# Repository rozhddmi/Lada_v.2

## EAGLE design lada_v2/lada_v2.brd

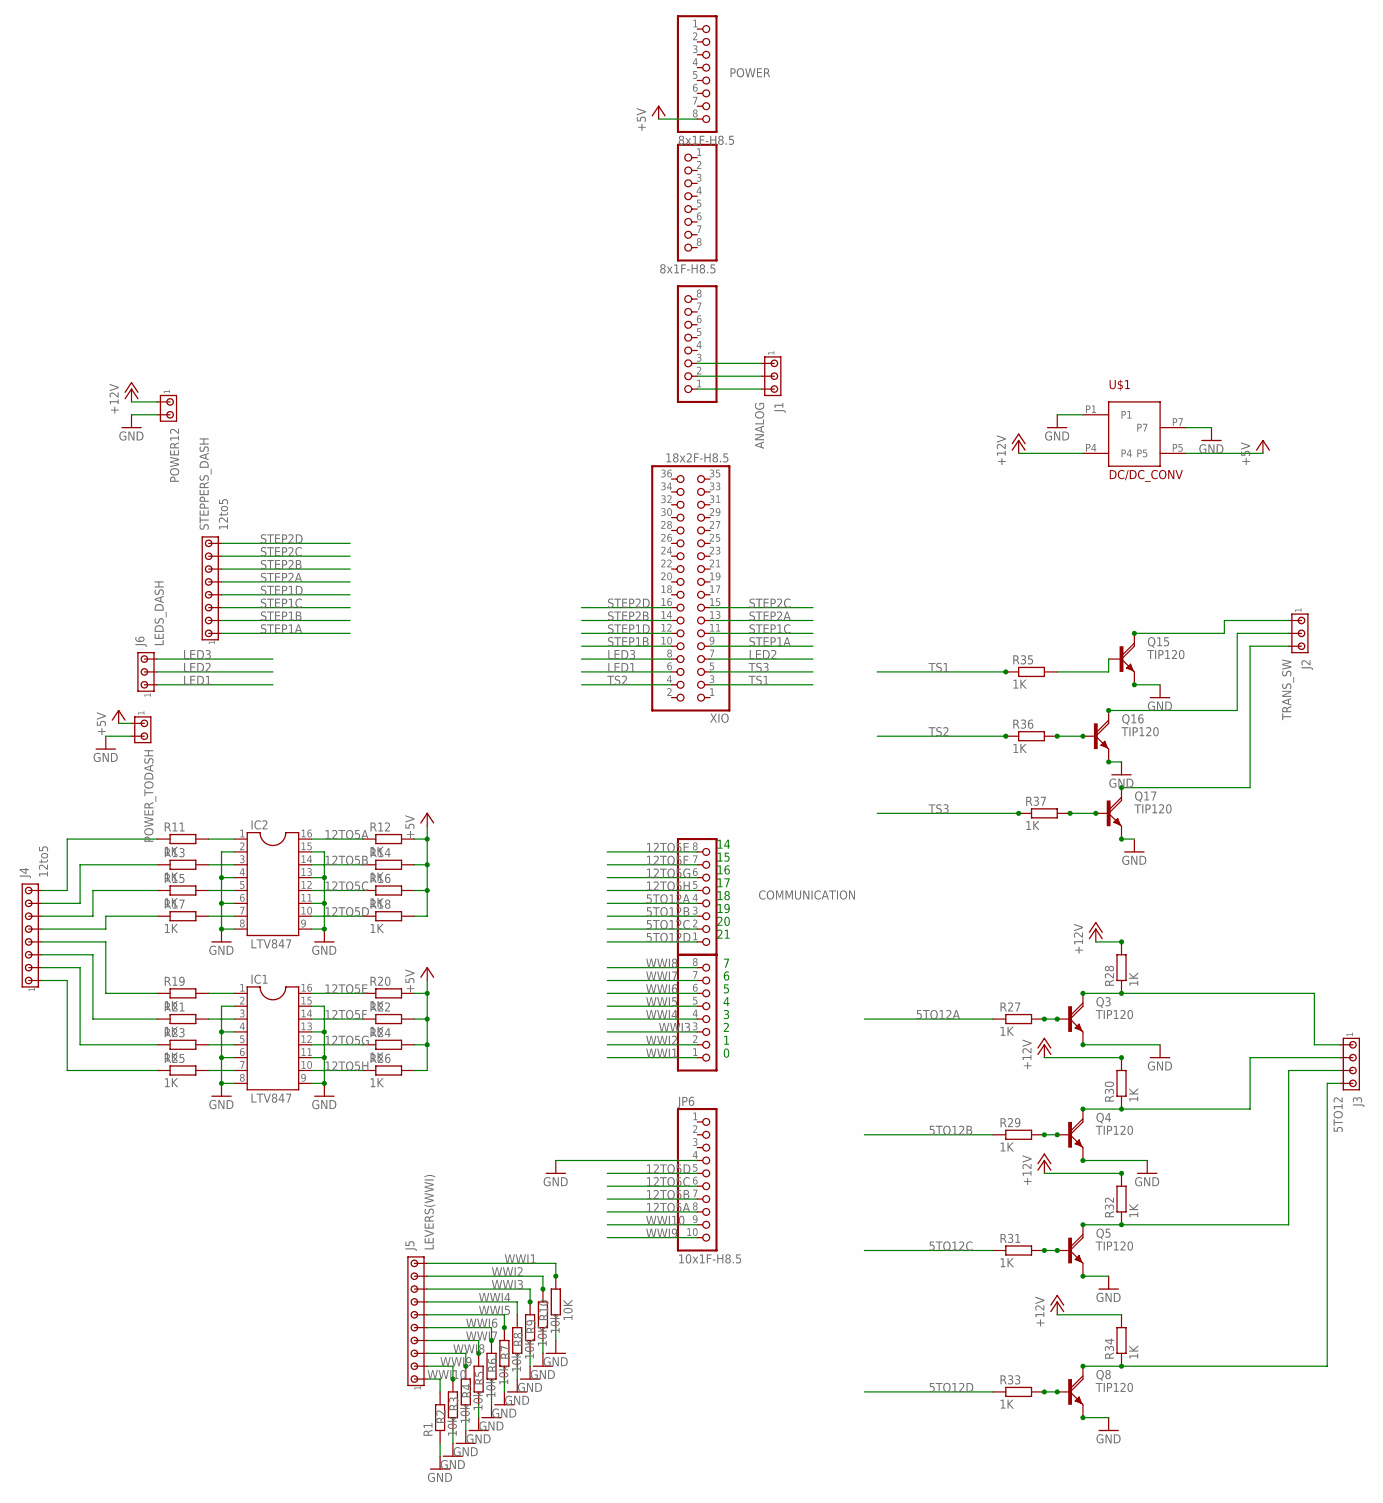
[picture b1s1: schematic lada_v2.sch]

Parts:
ADCH: 8x1F-H8.5; 1X08
ADCL: 8x1F-H8.5; 1X08
COMMUNICATION: 8x1F-H8.5; 1X08
IC1, IC2: LTV847; DIL16
J1: ANALOG; 10X03MTA
J2: TRANS_SW; 10X03MTA
J3: 5TO12; 10X04MTA
J4: 12to5; 10X08MTA
J5: LEVERS(WWI); 10X10MTA
J6: LEDS_DASH; 10X03MTA
JP6: 10x1F-H8.5; 1X10
POWER: 8x1F-H8.5; 1X08
POWER12: MTA02-100; 10X02MTA
POWER_TODASH: MTA02-100; 10X02MTA
PWML: 8x1F-H8.5; 1X08
Q3, Q4, Q5, Q8, Q15, Q16, Q17: TIP120; TO220AH
R1, R2, R3, R4, R5, R6, R9: 10k; 0207/10
R7, R8, R10: 10K; 0207/10
R11, R12, R13, R14, R15, R16, R17, R18, R19, R20, R21, R22, R23, R24, R25, R26, R27, R28, R29, R30, R31, R32, R33, R34, R35, R36, R37: 1K; 0207/10
STEPPERS_DASH: 12to5; 10X08MTA
U$1: DC/DC_CONV
XIO: 18x2F-H8.5; 2X18

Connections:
5TO12A: COMMUNICATION.4, R27.1
5TO12B: COMMUNICATION.3, R29.1
5TO12C: COMMUNICATION.2, R31.1
5TO12D: COMMUNICATION.1, R33.1
12TO5A: IC2.16, JP6.8, R12.1
12TO5B: IC2.14, JP6.7, R14.1
12TO5C: IC2.12, JP6.6, R16.1
12TO5D: IC2.10, JP6.5, R18.1
12TO5E: COMMUNICATION.8, IC1.16, R20.1
12TO5F: COMMUNICATION.7, IC1.14, R22.1
12TO5G: COMMUNICATION.6, IC1.12, R24.1
12TO5H: COMMUNICATION.5, IC1.10, R26.1
+5V: POWER.8, POWER_TODASH.1, R12.2, R14.2, R16.2, R18.2, R20.2, R22.2, R24.2, R26.2, U$1.P5
+12V: POWER12.1, R28.2, R30.2, R32.2, R34.2, U$1.P4
GND: IC1.2, IC1.4, IC1.6, IC1.8, IC1.9, IC1.11, IC1.13, IC1.15, IC2.2, IC2.4, IC2.6, IC2.8, IC2.9, IC2.11, IC2.13, IC2.15, JP6.4, POWER12.2, POWER_TODASH.2, Q3.E, Q4.E, Q5.E, Q8.E, Q15.E, Q16.E, Q17.E, R1.1, R2.1, R3.1, R4.1, R5.1, R6.1, R7.1, R8.1, R9.1, R10.1, U$1.P1, U$1.P7
LED1: J6.1, XIO.6
LED2: J6.2, XIO.7
LED3: J6.3, XIO.8
unnamed: ADCH.1, J1.3
unnamed: Q15.B, R35.2
unnamed: ADCH.2, J1.2
unnamed: ADCH.3, J1.1
unnamed: J3.1, Q3.C, R28.1
unnamed: J3.2, Q4.C, R30.1
unnamed: J3.3, Q5.C, R32.1
unnamed: Q5.B, R31.2
unnamed: Q4.B, R29.2
unnamed: Q3.B, R27.2
unnamed: J3.4, Q8.C, R34.1
unnamed: Q8.B, R33.2
unnamed: J2.1, Q15.C
unnamed: J2.2, Q16.C
unnamed: Q16.B, R36.2
unnamed: J2.3, Q17.C
unnamed: Q17.B, R37.2
unnamed: IC1.1, R19.2
unnamed: IC1.3, R21.2
unnamed: IC1.5, R23.2
unnamed: IC1.7, R25.2
unnamed: IC2.1, R11.2
unnamed: IC2.3, R13.2
unnamed: IC2.5, R15.2
unnamed: IC2.7, R17.2
unnamed: J4.8, R11.1
unnamed: J4.7, R13.1
unnamed: J4.6, R15.1
unnamed: J4.5, R17.1
unnamed: J4.4, R19.1
unnamed: J4.3, R21.1
unnamed: J4.2, R23.1
unnamed: J4.1, R25.1
STEP1A: STEPPERS_DASH.1, XIO.9
STEP1B: STEPPERS_DASH.2, XIO.10
STEP1C: STEPPERS_DASH.3, XIO.11
STEP1D: STEPPERS_DASH.4, XIO.12
STEP2A: STEPPERS_DASH.5, XIO.13
STEP2B: STEPPERS_DASH.6, XIO.14
STEP2C: STEPPERS_DASH.7, XIO.15
STEP2D: STEPPERS_DASH.8, XIO.16
TS1: R35.1, XIO.3
TS2: R36.1, XIO.4
TS3: R37.1, XIO.5
WWI1: J5.10, PWML.1, R10.2
WWI2: J5.9, PWML.2, R9.2
WWI3: J5.8, PWML.3, R8.2
WWI4: J5.7, PWML.4, R7.2
WWI5: J5.6, PWML.5, R6.2
WWI6: J5.5, PWML.6, R5.2
WWI7: J5.4, PWML.7, R4.2
WWI8: J5.3, PWML.8, R3.2
WWI9: J5.2, JP6.10, R2.2
WWI10: J5.1, JP6.9, R1.2

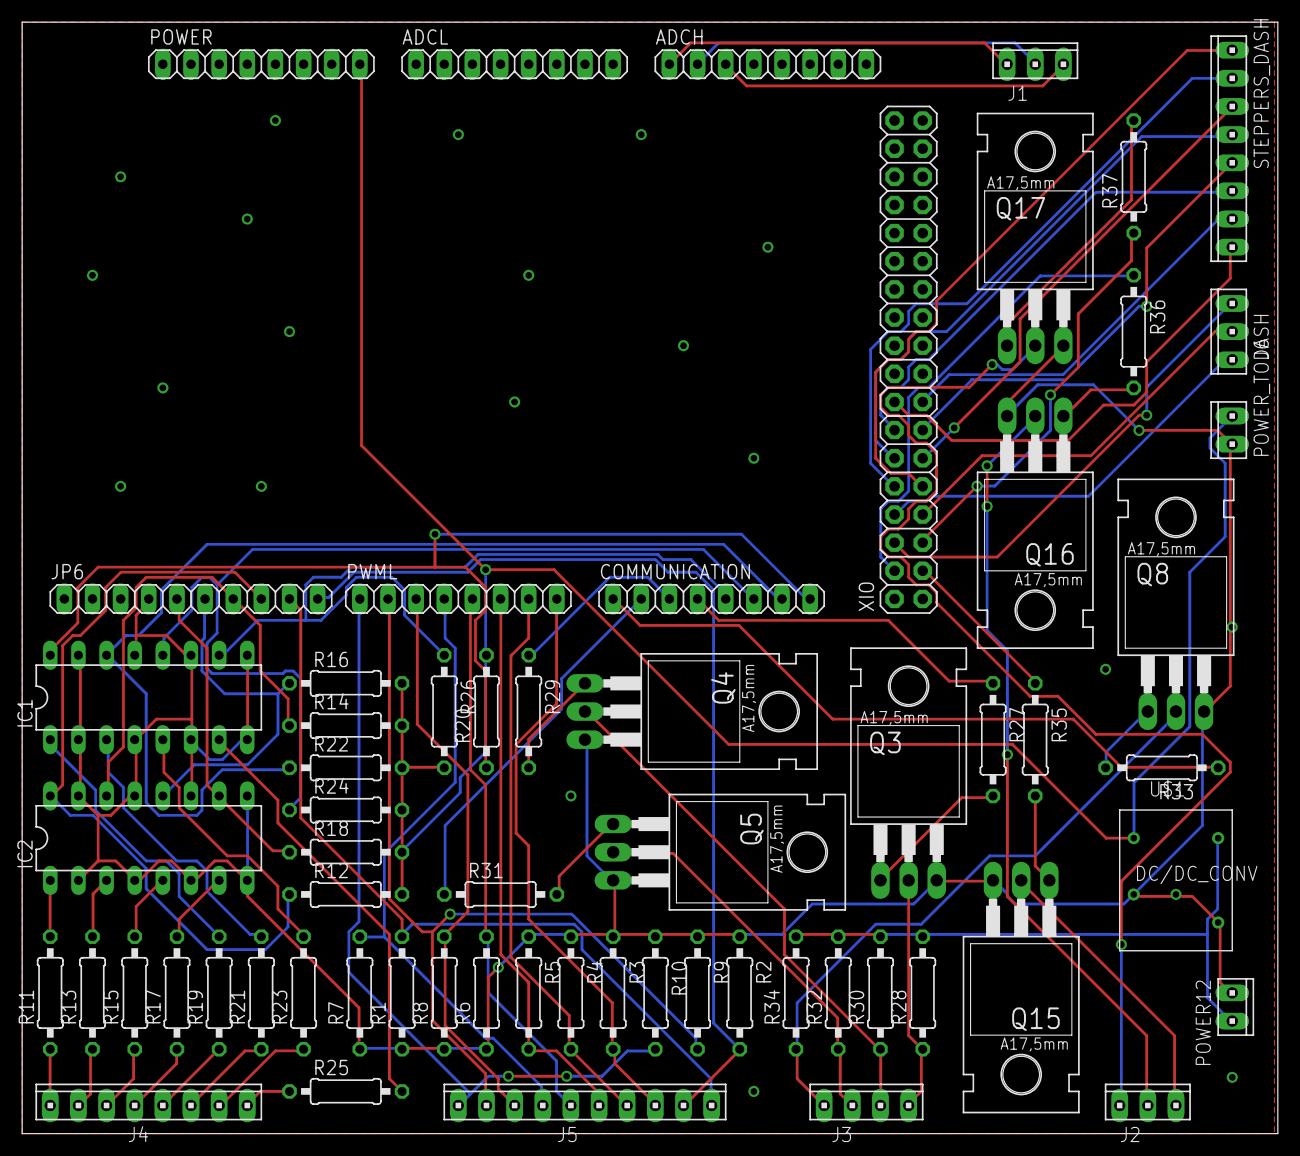
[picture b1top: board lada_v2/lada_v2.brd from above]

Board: 2 copper layers, 113.3 x 100.3 mm, 63 parts (0 on the bottom side), 72 nets.

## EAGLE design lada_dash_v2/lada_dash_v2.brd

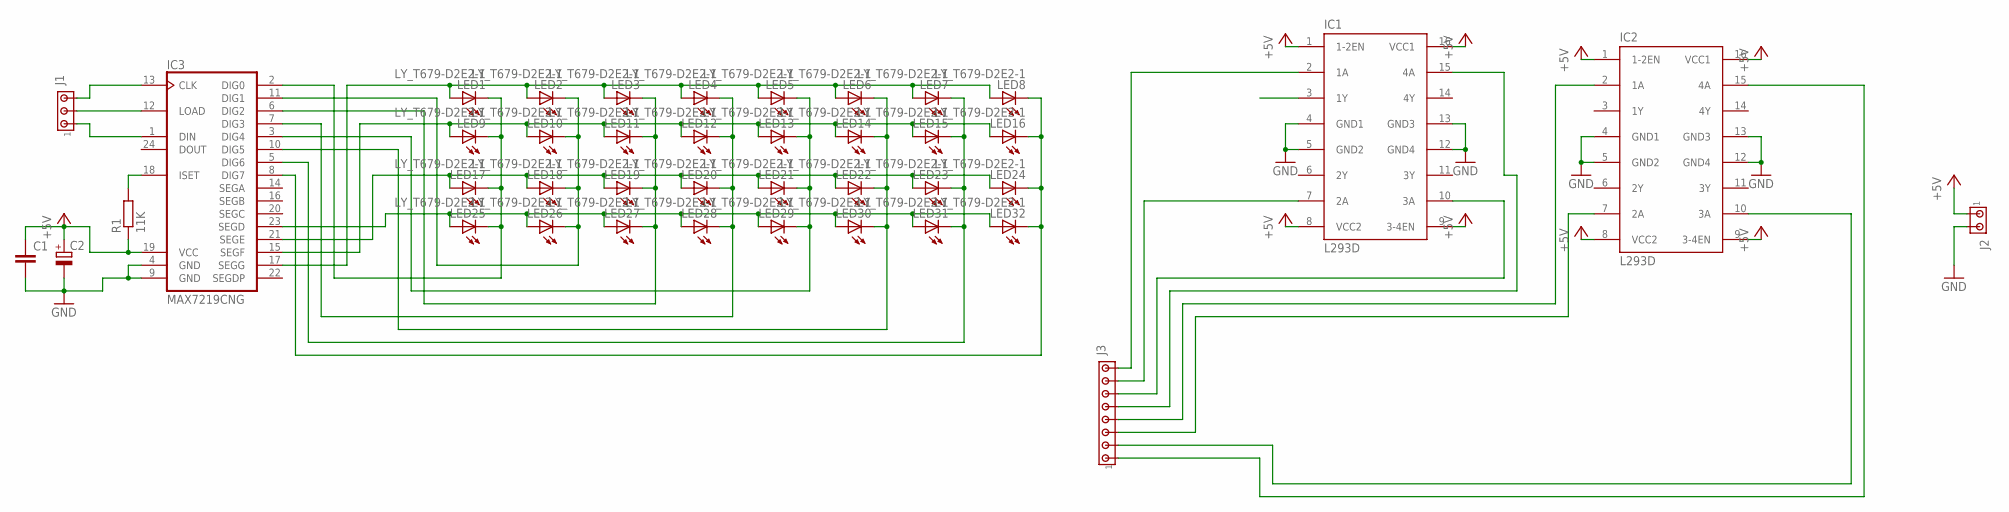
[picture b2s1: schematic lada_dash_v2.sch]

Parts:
C1: C-EU025-025X050; C025-025X050
C2: CPOL-EUE2.5-5; E2,5-5
IC1, IC2: L293D; DIL16
IC3: MAX7219CNG; DIL24-3
J1: MTA03-100; 10X03MTA
J2: MTA02-100; 10X02MTA
J3: MTA08-100; 10X08MTA
LED1, LED2, LED3, LED4, LED5, LED6, LED7, LED8, LED9, LED10, LED11, LED12, LED13, LED14, LED15, LED16, LED17, LED18, LED19, LED20, LED21, LED22, LED23, LED24, LED25, LED26, LED27, LED28, LED29, LED30, LED31, LED32: LY_T679-D2E2-1; PLCC2
R1: 11K; 0207/10

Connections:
+5V: C1.1, C2.+, IC1.1 (1-2EN), IC1.8 (VCC2), IC1.9 (3-4EN), IC1.16 (VCC1), IC2.1 (1-2EN), IC2.8 (VCC2), IC2.9 (3-4EN), IC2.16 (VCC1), IC3.19 (VCC), J2.1, R1.1
GND: C1.2, C2.-, IC1.4 (GND1), IC1.5 (GND2), IC1.12 (GND4), IC1.13 (GND3), IC2.4 (GND1), IC2.5 (GND2), IC2.12 (GND4), IC2.13 (GND3), IC3.4 (GND), IC3.9 (GND), J2.2
unnamed: IC3.17 (SEGG), LED1.A, LED2.A, LED3.A, LED4.A, LED5.A, LED6.A, LED7.A, LED8.A
unnamed: IC3.15 (SEGF), LED9.A, LED10.A, LED11.A, LED12.A, LED13.A, LED14.A, LED15.A, LED16.A
unnamed: IC3.21 (SEGE), LED17.A, LED18.A, LED19.A, LED20.A, LED21.A, LED22.A, LED23.A, LED24.A
unnamed: IC3.23 (SEGD), LED25.A, LED26.A, LED27.A, LED28.A, LED29.A, LED30.A, LED31.A, LED32.A
unnamed: IC3.2 (DIG0), LED1.C, LED9.C, LED17.C, LED25.C
unnamed: IC3.11 (DIG1), LED2.C, LED10.C, LED18.C, LED26.C
unnamed: IC3.6 (DIG2), LED3.C, LED11.C, LED19.C, LED27.C
unnamed: IC3.7 (DIG3), LED4.C, LED12.C, LED20.C, LED28.C
unnamed: IC3.3 (DIG4), LED5.C, LED13.C, LED21.C, LED29.C
unnamed: IC3.10 (DIG5), LED6.C, LED14.C, LED22.C, LED30.C
unnamed: IC3.5 (DIG6), LED7.C, LED15.C, LED23.C, LED31.C
unnamed: IC3.8 (DIG7), LED8.C, LED16.C, LED24.C, LED32.C
unnamed: IC3.13 (CLK), J1.3
unnamed: IC3.12 (LOAD), J1.2
unnamed: IC3.1 (DIN), J1.1
unnamed: IC1.2 (1A), J3.8
unnamed: IC1.7 (2A), J3.7
unnamed: IC1.10 (3A), J3.6
unnamed: IC1.15 (4A), J3.5
unnamed: IC2.2 (1A), J3.4
unnamed: IC2.7 (2A), J3.3
unnamed: IC2.10 (3A), J3.2
unnamed: IC2.15 (4A), J3.1
unnamed: IC3.18 (ISET), R1.2

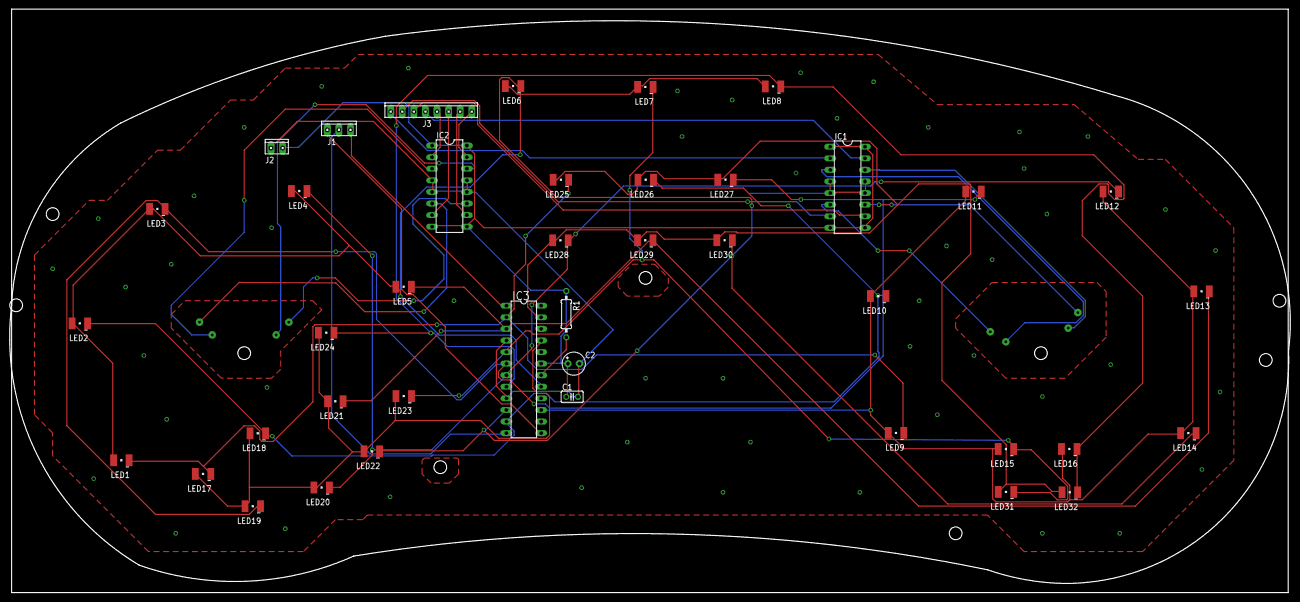
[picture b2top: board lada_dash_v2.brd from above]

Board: 2 copper layers, 280.8 x 127.9 mm, 41 parts (0 on the bottom side), 26 nets.

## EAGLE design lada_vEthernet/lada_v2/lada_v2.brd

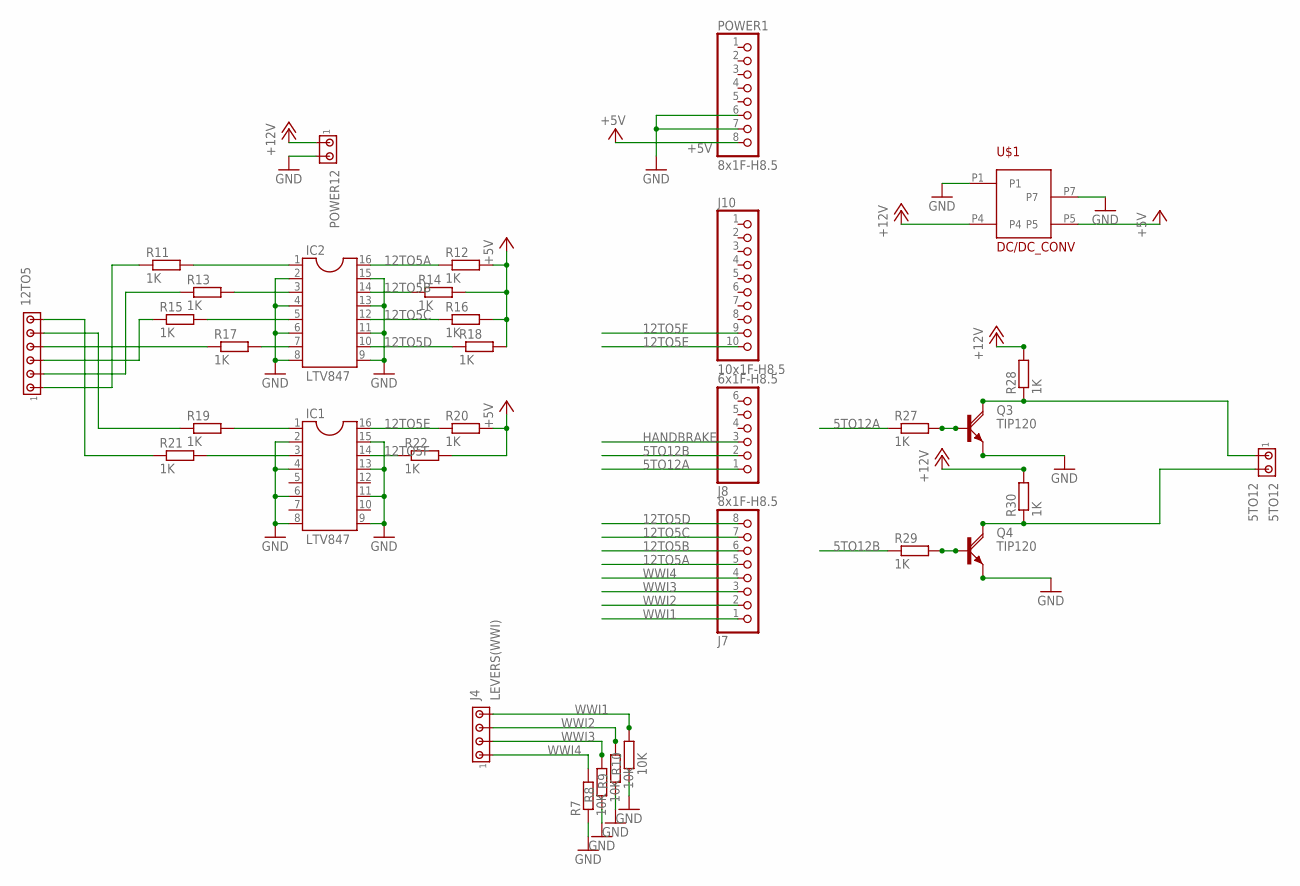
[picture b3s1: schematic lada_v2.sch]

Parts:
5TO12: 5TO12; 10X02MTA
12TO5: MTA06-100; 10X06MTA
IC1, IC2: LTV847; DIL16
J4: LEVERS(WWI); 10X04MTA
J7: 8x1F-H8.5; 1X08
J8: 6x1F-H8.5; 1X06
J10: 10x1F-H8.5; 1X10
POWER1: 8x1F-H8.5; 1X08
POWER12: MTA02-100; 10X02MTA
Q3, Q4: TIP120; TO220AH
R7, R8, R10: 10K; 0207/10
R9: 10k; 0207/10
R11, R12, R13, R14, R15, R16, R17, R18, R19, R20, R21, R22, R27, R28, R29, R30: 1K; 0207/10
U$1: DC/DC_CONV

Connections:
5TO12A: J8.1, R27.1
5TO12B: J8.2, R29.1
12TO5A: IC2.16, J7.5, R12.1
12TO5B: IC2.14, J7.6, R14.1
12TO5C: IC2.12, J7.7, R16.1
12TO5D: IC2.10, J7.8, R18.1
12TO5E: IC1.16, J10.10, R20.1
12TO5F: IC1.14, J10.9, R22.1
+5V: POWER1.8, R12.2, R14.2, R16.2, R18.2, R20.2, R22.2, U$1.P5
+12V: POWER12.1, R28.2, R30.2, U$1.P4
GND: IC1.2, IC1.4, IC1.6, IC1.8, IC1.9, IC1.11, IC1.13, IC1.15, IC2.2, IC2.4, IC2.6, IC2.8, IC2.9, IC2.11, IC2.13, IC2.15, POWER1.6, POWER1.7, POWER12.2, Q3.E, Q4.E, R7.1, R8.1, R9.1, R10.1, U$1.P1, U$1.P7
HANDBRAKE: J8.3
unnamed: 5TO12.1, Q3.C, R28.1
unnamed: 5TO12.2, Q4.C, R30.1
unnamed: Q4.B, R29.2
unnamed: Q3.B, R27.2
unnamed: IC1.1, R19.2
unnamed: IC1.3, R21.2
unnamed: IC2.1, R11.2
unnamed: IC2.3, R13.2
unnamed: IC2.5, R15.2
unnamed: IC2.7, R17.2
unnamed: 12TO5.1, R11.1
unnamed: 12TO5.2, R13.1
unnamed: 12TO5.3, R15.1
unnamed: 12TO5.4, R17.1
unnamed: 12TO5.5, R19.1
unnamed: 12TO5.6, R21.1
WWI1: J4.4, J7.1, R10.2
WWI2: J4.3, J7.2, R9.2
WWI3: J4.2, J7.3, R8.2
WWI4: J4.1, J7.4, R7.2

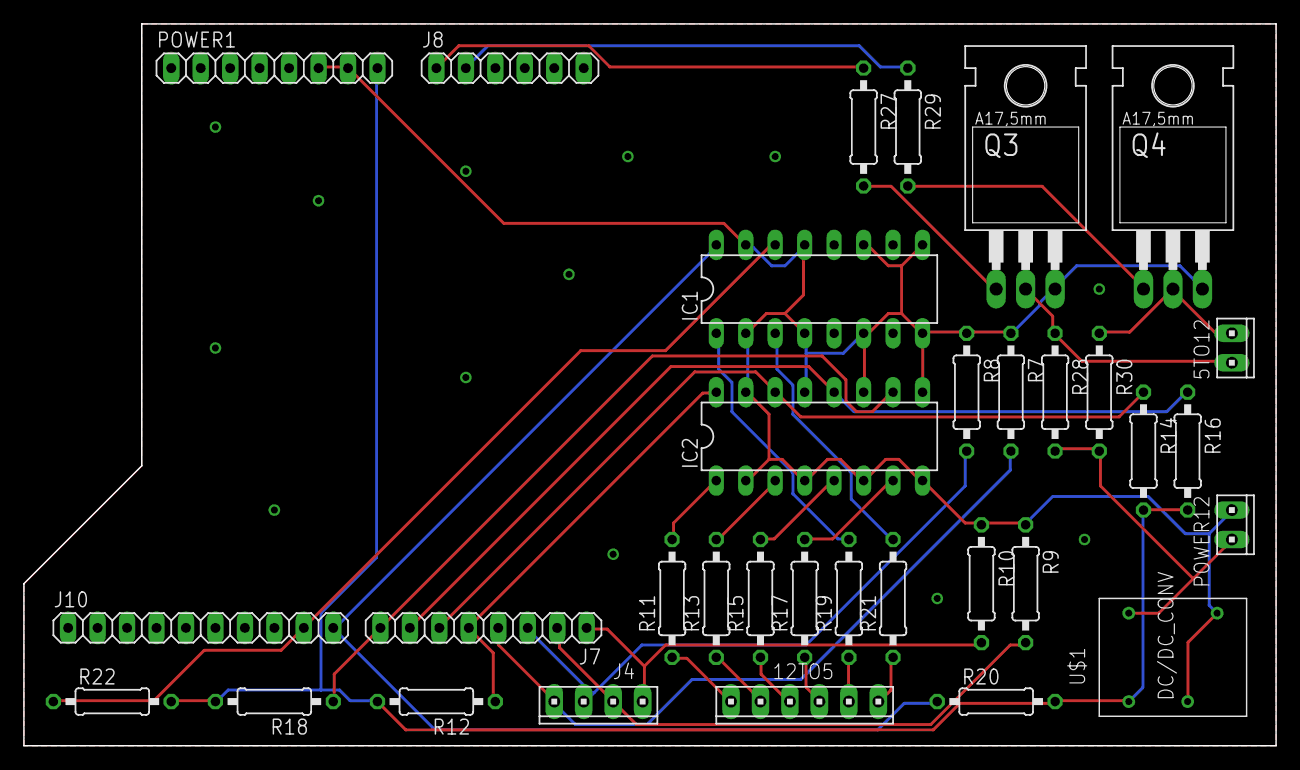
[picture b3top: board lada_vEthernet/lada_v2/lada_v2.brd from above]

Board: 2 copper layers, 108.0 x 62.2 mm, 33 parts (0 on the bottom side), 31 nets.

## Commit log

2017-04-12 :neckbeard: Added .gitattributes
2017-04-24 dr14: unpack, addng arduino progect
2017-05-01 dr14: adding led test project
2017-06-19 dr14: adding a stepper test, changing led adresses to the latest schamatics
2017-08-16 dr14: latest for lada2
2019-02-14 dr14: LAtest lockal changes
